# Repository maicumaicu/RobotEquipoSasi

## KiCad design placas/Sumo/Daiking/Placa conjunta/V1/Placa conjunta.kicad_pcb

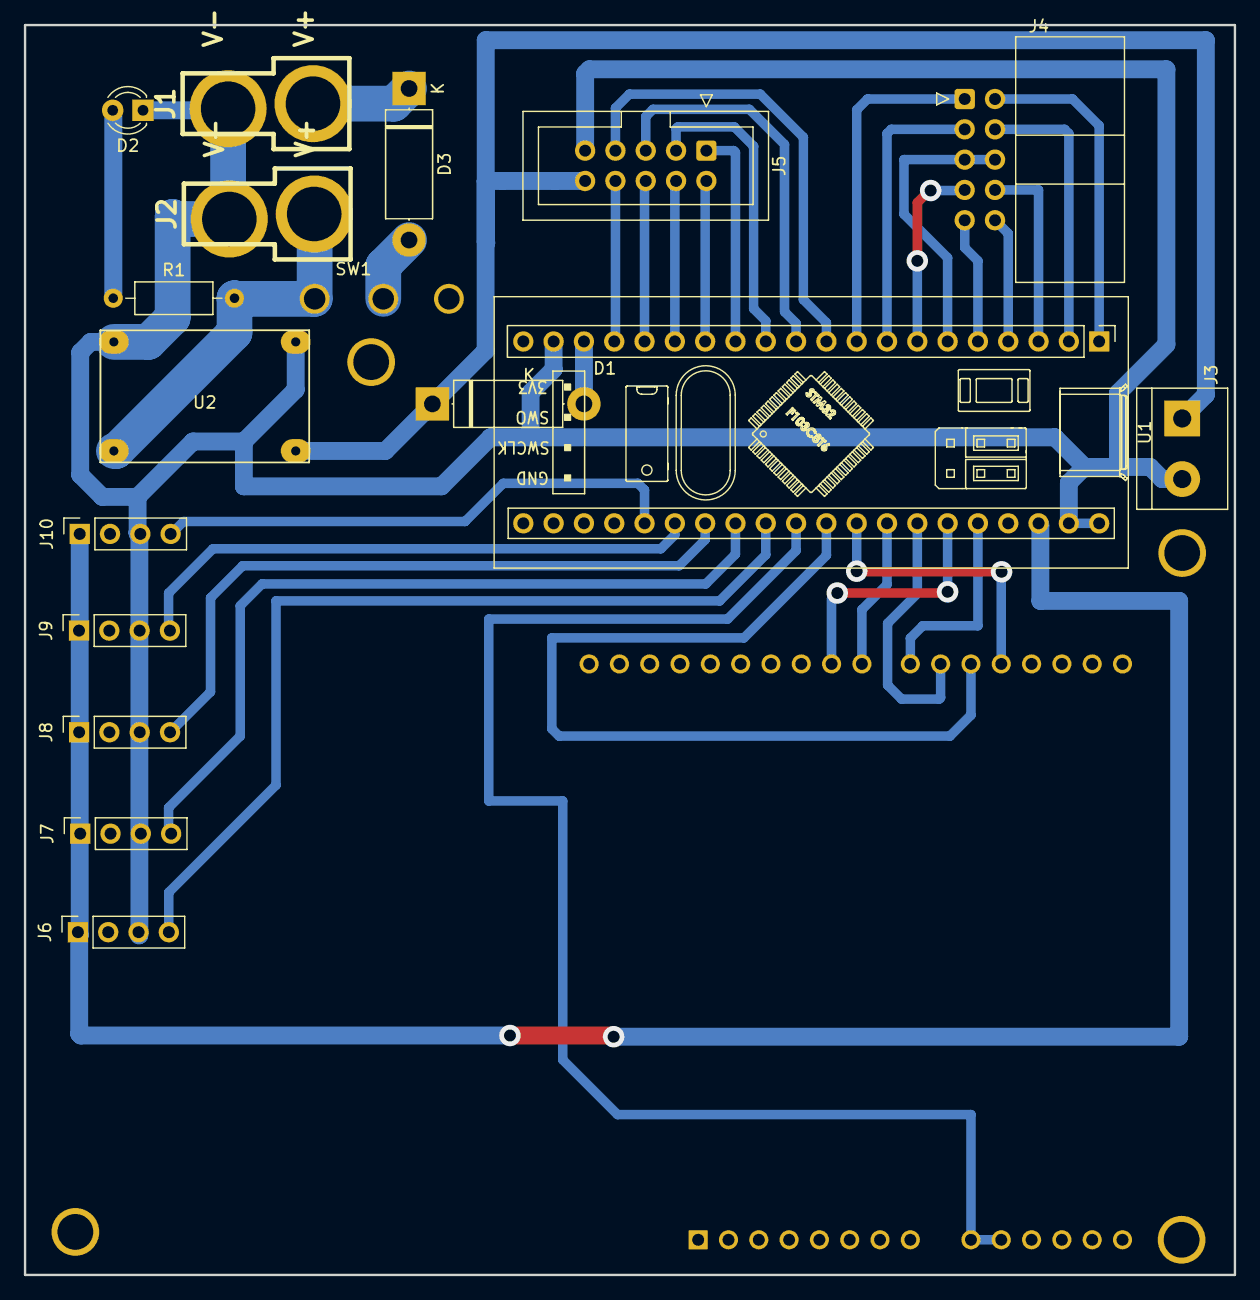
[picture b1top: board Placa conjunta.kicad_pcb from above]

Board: 2 copper layers, 101.4 x 104.7 mm, 18 parts (1 on the bottom side), 37 nets.

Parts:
A1: Arduino_UNO_R3
D1, D3: type="D" model="DIODE" lib=""; D_5W_P12.70mm_Horizontal
D2: LED; LED_D3.0mm
J1: BATERIA1; DEANS
J2: MOTORES; DEANS
J3: Conn_01x02_Male; TerminalBlock_bornier-2_P5.08mm
J4: Control Sensores; IDC-Header_2x05_P2.54mm_Horizontal
J5: Control Botones; IDC-Header_2x05_P2.54mm_Vertical
J6, J7, J8, J9, J10: Conn_01x04_Male; PinSocket_1x04_P2.54mm_Vertical
R1: R; R_Axial_DIN0207_L6.3mm_D2.5mm_P10.16mm_Horizontal
SW1: SW_DPDT_x2; Banana_Jack_3Pin
U1: YAAJ_BluePill_Part_Like_SWD_Breakout; YAAJ_BluePill_1
U2: Mini360; Mini360_step-down

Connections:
/3,3v: J6.1, J7.1, J8.1, J9.1, J10.1, U1.20 (3V3), U1.38 (3V3)
/5v: D1.1 (A), J3.1, J5.10, U2.4 (OUT+)
/38khz: J4.5, J4.6, U1.6 (PA9)
/B1: J5.1, U1.13 (PB5)
/B2: J5.3, U1.12 (PB4)
/B3: J5.5, U1.11 (PB3)
/B4: J5.7, U1.10 (PA15)
/EN1: A1.9 (A0), A1.10 (A1), U1.30 (PA5)
/INA1: A1.22 (D7), U1.36 (PB11)
/INA2: A1.23 (D8), U1.33 (PB0)
/INB1: A1.19 (D4), U1.32 (PA7)
/INB2: A1.24 (D9), U1.35 (PB10)
/L1: J5.2, U1.14 (PB6)
/L2: J5.4, U1.15 (PB7)
/L3: J5.6, U1.16 (PB8)
/L4: J5.8, U1.17 (PB9)
/P1: J6.4, U1.29 (PA4)
/P2: J7.4, U1.28 (PA3)
/P3: J8.4, U1.27 (PA2)
/P4: J9.4, U1.26 (PA1)
/P5: J10.4, U1.25 (PA0)
/PWM1: A1.20 (D5), U1.31 (PA6)
/PWM2: A1.21 (D6), U1.34 (PB1)
/S1: J4.9, U1.5 (PA8)
/S2: J4.7, U1.7 (PA10)
/S3: J4.3, U1.8 (PA11)
/S4: J4.1, U1.9 (PA12)
/S5: J4.10, U1.4 (PB15)
/S6: J4.8, U1.3 (PB14)
/S7: J4.4, U1.2 (PB13)
/S8: J4.2, U1.1 (PB12)
/VCC: D3.1 (A), J1.1
/VIN: J2.1, R1.2, SW1.1 (A), U2.2 (IN+)
GND: D2.1 (K), J1.2, J2.2, J3.2, J5.9, J6.3, J7.3, J8.3, J9.3, J10.3, U1.19 (GND), U1.39 (GND), U1.40 (GND), U2.1 (IN-), U2.3 (OUT-)
unnamed: D1.2 (K), U1.18 (5V)
unnamed: D2.2 (A), R1.1
unnamed: D3.2 (K), SW1.2 (B)

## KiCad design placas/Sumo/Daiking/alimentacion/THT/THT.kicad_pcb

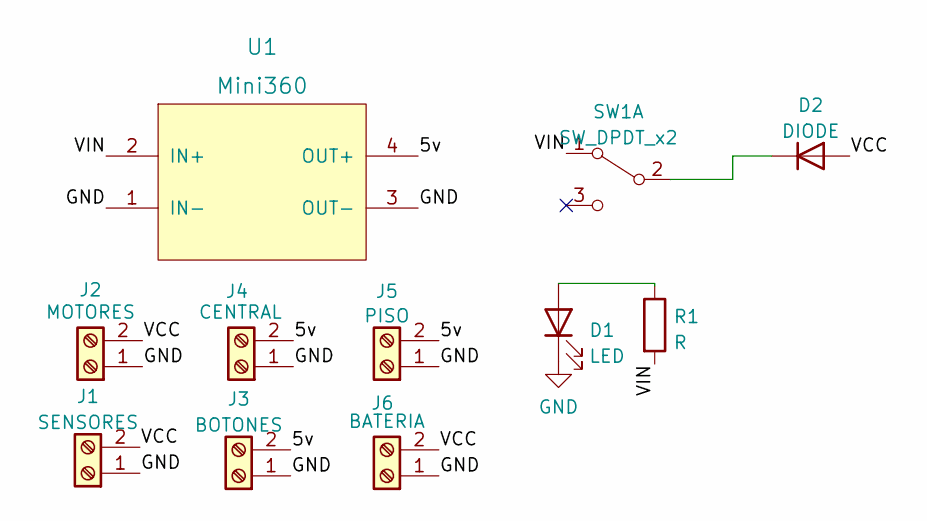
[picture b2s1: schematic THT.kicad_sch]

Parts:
D1: LED; LED_D3.0mm
D2: DIODE; D_5W_P12.70mm_Horizontal
J1: SENSORES; TerminalBlock_bornier-2_P5.08mm
J2: MOTORES; AMASS_XT30U-F_1x02_P5.0mm_Vertical
J3: BOTONES; TerminalBlock_bornier-2_P5.08mm
J4: CENTRAL; TerminalBlock_bornier-2_P5.08mm
J5: PISO; TerminalBlock_bornier-2_P5.08mm
J6: BATERIA; AMASS_XT30U-F_1x02_P5.0mm_Vertical
R1: R; R_Axial_DIN0207_L6.3mm_D2.5mm_P10.16mm_Horizontal
SW1: SW_DPDT_x2; SW_Slide_1P2T_CK_OS102011MS2Q
U1: Mini360; Mini360_step-down

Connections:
/5v: J3.2, J4.2, J5.2, U1.4 (OUT+)
/VCC: D2.1 (A), J1.2, J2.2, J6.2
/VIN: R1.2, SW1.1 (A), U1.2 (IN+)
GND: D1.1 (K), J1.1, J2.1, J3.1, J4.1, J5.1, J6.1, U1.1 (IN-), U1.3 (OUT-)
unnamed: D1.2 (A), R1.1
unnamed: D2.2 (K), SW1.2 (B)

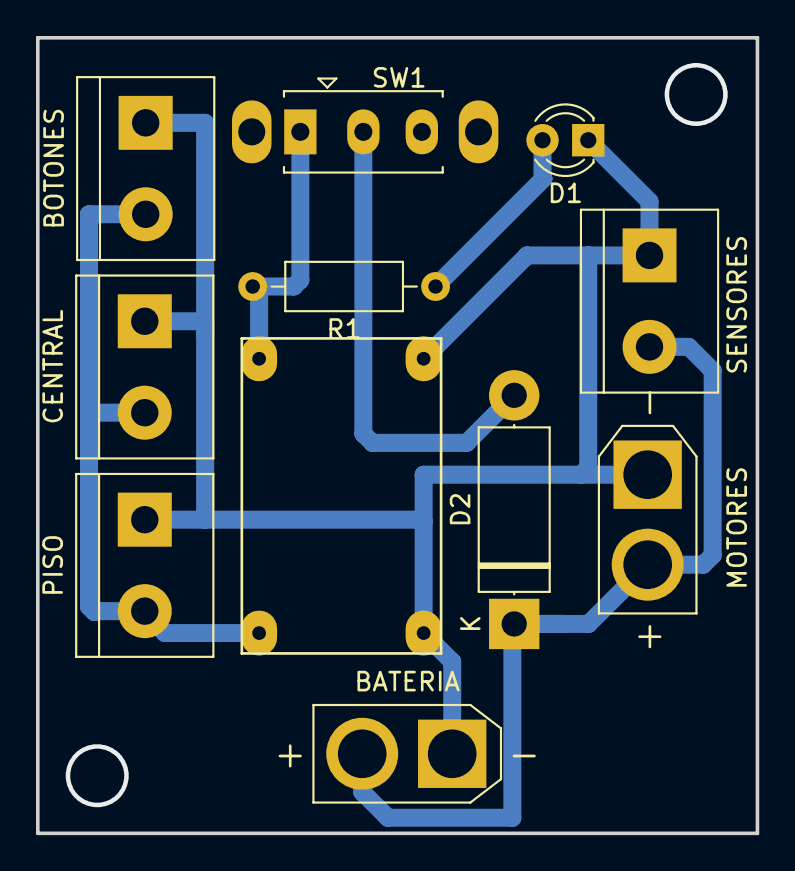
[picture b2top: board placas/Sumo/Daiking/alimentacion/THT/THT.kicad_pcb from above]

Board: 2 copper layers, 40.0 x 44.2 mm, 11 parts (0 on the bottom side), 6 nets.

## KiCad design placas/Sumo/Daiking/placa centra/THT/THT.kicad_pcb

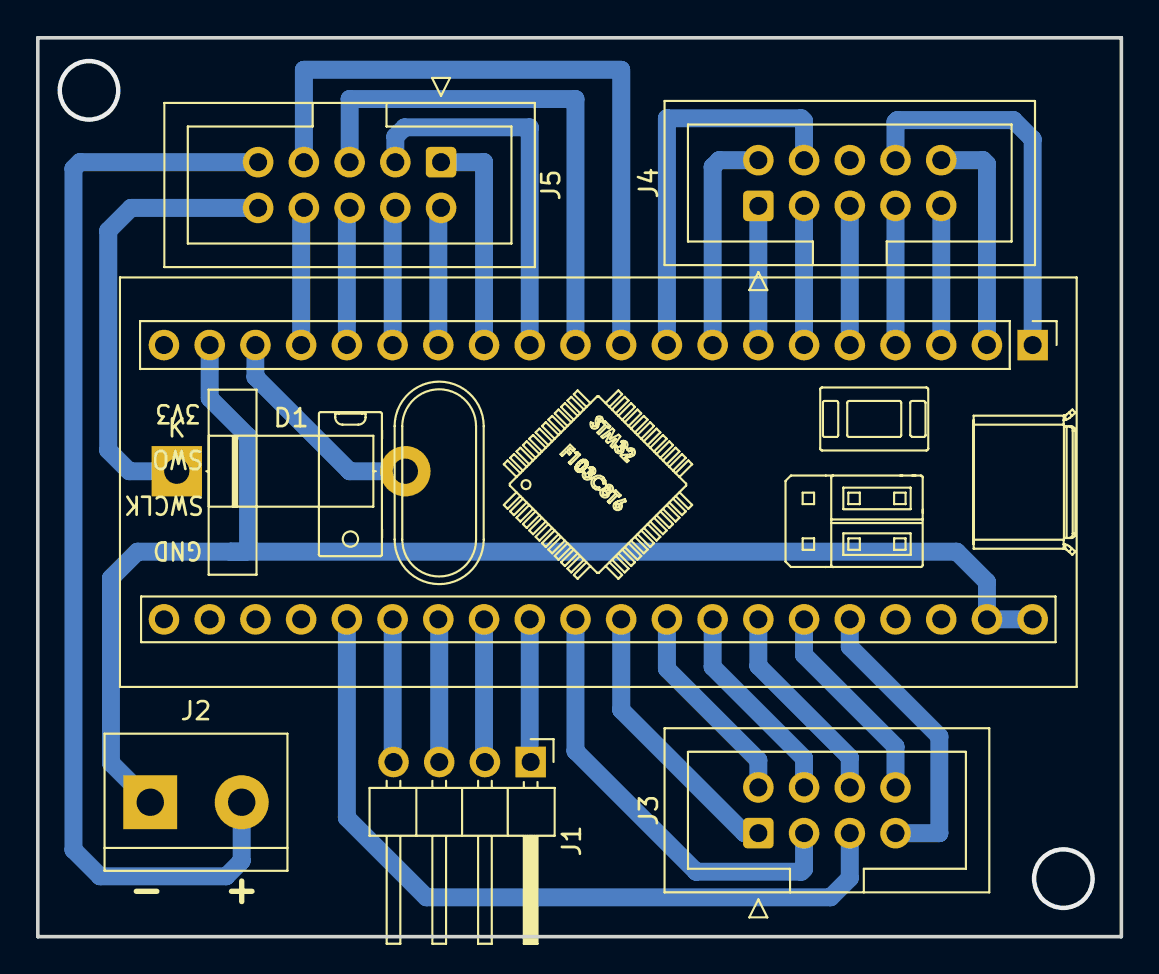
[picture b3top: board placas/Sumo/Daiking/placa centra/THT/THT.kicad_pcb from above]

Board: 2 copper layers, 60.2 x 49.9 mm, 7 parts (0 on the bottom side), 33 nets.

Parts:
D1: DIODE; D_5W_P12.70mm_Horizontal
J1: Control Piso; PinHeader_1x04_P2.54mm_Horizontal
J2: BATERIA; TerminalBlock_bornier-2_P5.08mm
J3: Control Motores; IDC-Header_2x04_P2.54mm_Vertical
J4: Control Sensores; IDC-Header_2x05_P2.54mm_Vertical
J5: Control Botones; IDC-Header_2x05_P2.54mm_Vertical
U1: YAAJ_BluePill_Part_Like_SWD_Breakout; YAAJ_BluePill_SWD_1

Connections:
/5v: D1.2 (K), U1.18 (5V)
/38Kh: J4.5, U1.5 (PA8)
/B1: J5.1, U1.13 (PB5)
/B2: J5.3, U1.12 (PB4)
/B3: J5.5, U1.11 (PB3)
/B4: J5.7, U1.10 (PA15)
/E1: J2.2, J5.9
/E2: D1.1 (A), J5.10
/EN1: J3.3, U1.30 (PA5)
/EN2: J3.4, U1.33 (PB0)
/GND: J2.1, U1.19 (GND), U1.39 (GND), U1.40 (GND)
/INA1: J3.7, U1.36 (PB11)
/INA2: J3.2, U1.32 (PA7)
/INB1: J3.1, U1.31 (PA6)
/INB2: J3.8, U1.35 (PB10)
/L1: J5.2, U1.14 (PB6)
/L2: J5.4, U1.15 (PB7)
/L3: J5.6, U1.16 (PB8)
/L4: J5.8, U1.17 (PB9)
/P1: J1.1, U1.29 (PA4)
/P2: J1.2, U1.28 (PA3)
/P3: J1.3, U1.27 (PA2)
/P4: J1.4, U1.26 (PA1)
/PWM1: J3.5, U1.25 (PA0)
/PWM2: J3.6, U1.34 (PB1)
/S1: J4.3, U1.6 (PA9)
/S2: J4.1, U1.7 (PA10)
/S3: J4.2, U1.8 (PA11)
/S4: J4.4, U1.9 (PA12)
/S5: J4.7, U1.4 (PB15)
/S6: J4.9, U1.3 (PB14)
/S7: J4.10, U1.2 (PB13)
/S8: J4.8, U1.1 (PB12)

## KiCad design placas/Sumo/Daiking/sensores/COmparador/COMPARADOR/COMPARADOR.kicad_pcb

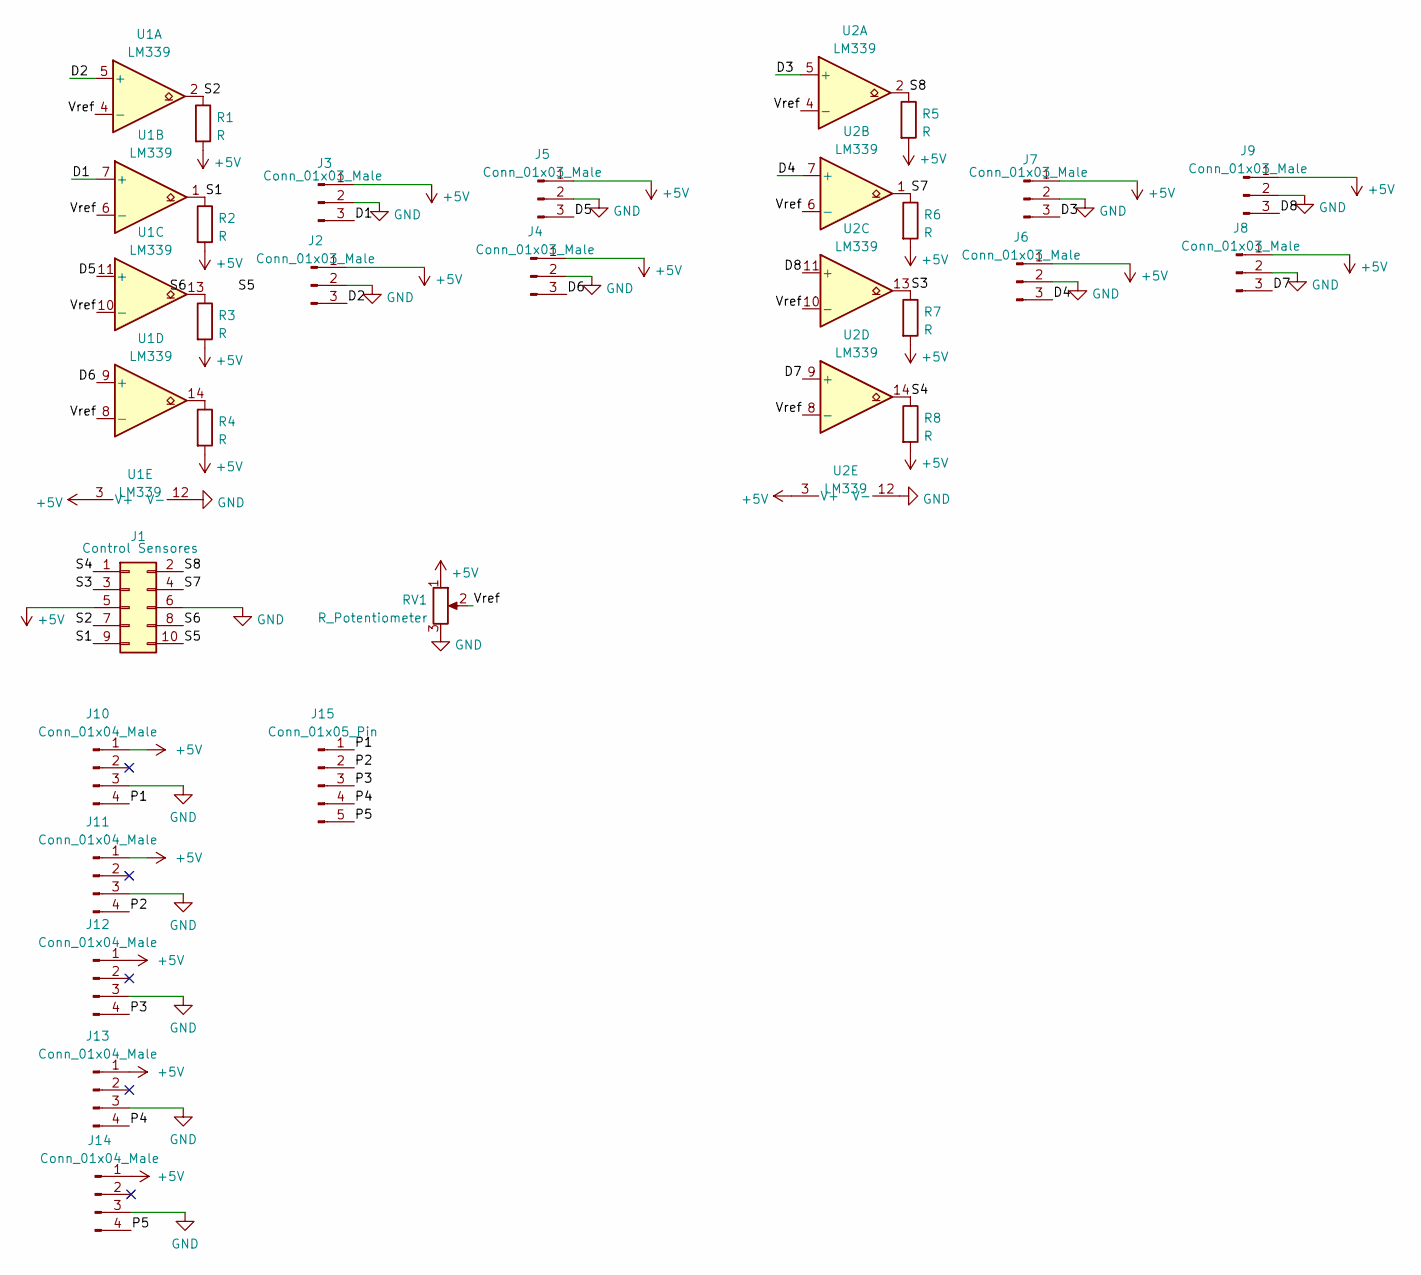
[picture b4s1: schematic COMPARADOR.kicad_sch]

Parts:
J1: Control Sensores; IDC-Header_2x05_P2.54mm_Horizontal
J2, J3, J4, J5, J6, J7, J8, J9: Conn_01x03_Male; PinHeader_1x03_P2.54mm_Vertical
J10, J11, J12, J13, J14: Conn_01x04_Male; PinSocket_1x04_P2.54mm_Vertical
J15: Conn_01x05_Pin; PinHeader_1x05_P2.54mm_Horizontal
R1, R2, R3, R4, R5, R6, R7, R8: R; R_Axial_DIN0207_L6.3mm_D2.5mm_P10.16mm_Horizontal
RV1: R_Potentiometer; Potentiometer_Bourns_3299W_Vertical
U1, U2: LM339; DIP-14_W7.62mm_Socket_LongPads

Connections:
+5V: J1.5, J2.1, J3.1, J4.1, J5.1, J6.1, J7.1, J8.1, J9.1, J10.1, J11.1, J12.1, J13.1, J14.1, R1.2, R2.2, R3.2, R4.2, R5.2, R6.2, R7.2, R8.2, RV1.1, U1.3 (V+), U2.3 (V+)
/D1: J3.3, U1.7 (+)
/D2: J2.3, U1.5 (+)
/D3: J7.3, U2.5 (+)
/D4: J6.3, U2.7 (+)
/D5: J5.3, U1.11 (+)
/D6: J4.3, U1.9 (+)
/D7: J8.3, U2.9 (+)
/D8: J9.3, U2.11 (+)
/P1: J10.4, J15.1
/P2: J11.4, J15.2
/P3: J12.4, J15.3
/P4: J13.4, J15.4
/P5: J14.4, J15.5
/S1: J1.9, R2.1, U1.1
/S2: J1.7, R1.1, U1.2
/S3: J1.3, R7.1, U2.13
/S4: J1.1, R8.1, U2.14
/S5: J1.10
/S6: J1.8
/S7: J1.4, R6.1, U2.1
/S8: J1.2, R5.1, U2.2
/Vref: RV1.2, U1.4 (-), U1.6 (-), U1.8 (-), U1.10 (-), U2.4 (-), U2.6 (-), U2.8 (-), U2.10 (-)
GND: J1.6, J2.2, J3.2, J4.2, J5.2, J6.2, J7.2, J8.2, J9.2, J10.3, J11.3, J12.3, J13.3, J14.3, RV1.3, U1.12 (V-), U2.12 (V-)
unnamed: R3.1, U1.13
unnamed: R4.1, U1.14

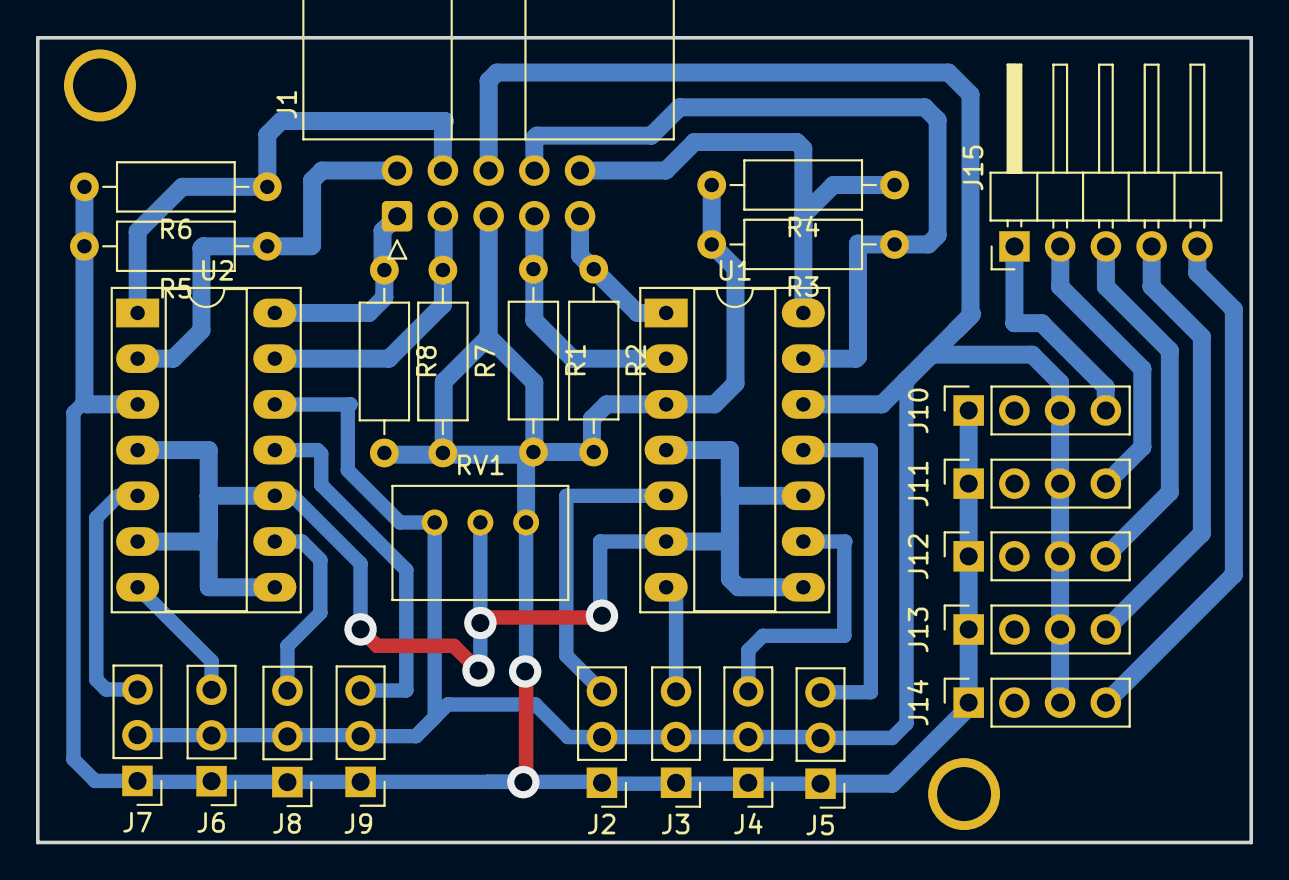
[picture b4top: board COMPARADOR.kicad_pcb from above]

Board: 2 copper layers, 67.4 x 44.7 mm, 26 parts (0 on the bottom side), 24 nets.

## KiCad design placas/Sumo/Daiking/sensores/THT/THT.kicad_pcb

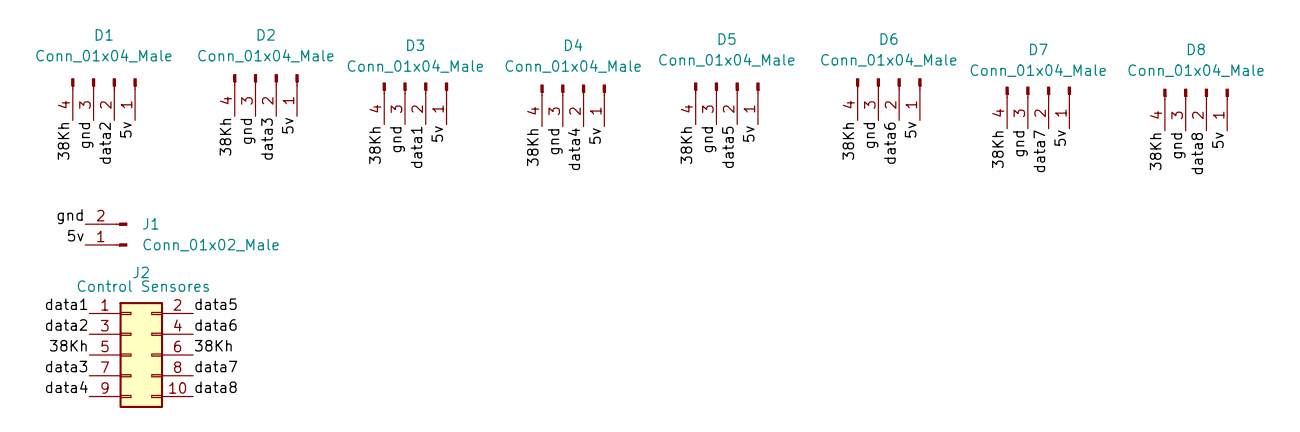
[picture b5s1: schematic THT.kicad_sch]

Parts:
D1, D2, D3, D4: Conn_01x04_Male
D5, D6, D7, D8: Conn_01x04_Male; PinHeader_1x04_P2.54mm_Vertical
J1: Conn_01x02_Male; TerminalBlock_bornier-2_P5.08mm
J2: Control Sensores; IDC-Header_2x05_P2.54mm_Vertical

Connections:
/5v: D1.1, D2.1, D3.1, D4.1, D5.1, D6.1, D7.1, D8.1, J1.1
/38Kh: D1.4, D2.4, D3.4, D4.4, D5.4, D6.4, D7.4, D8.4, J2.5, J2.6
/data1: D3.2, J2.1
/data2: D1.2, J2.3
/data3: D2.2, J2.7
/data4: D4.2, J2.9
/data5: D5.2, J2.2
/data6: D6.2, J2.4
/data7: D7.2, J2.8
/data8: D8.2, J2.10
/gnd: D1.3, D2.3, D3.3, D4.3, D5.3, D6.3, D7.3, D8.3, J1.2

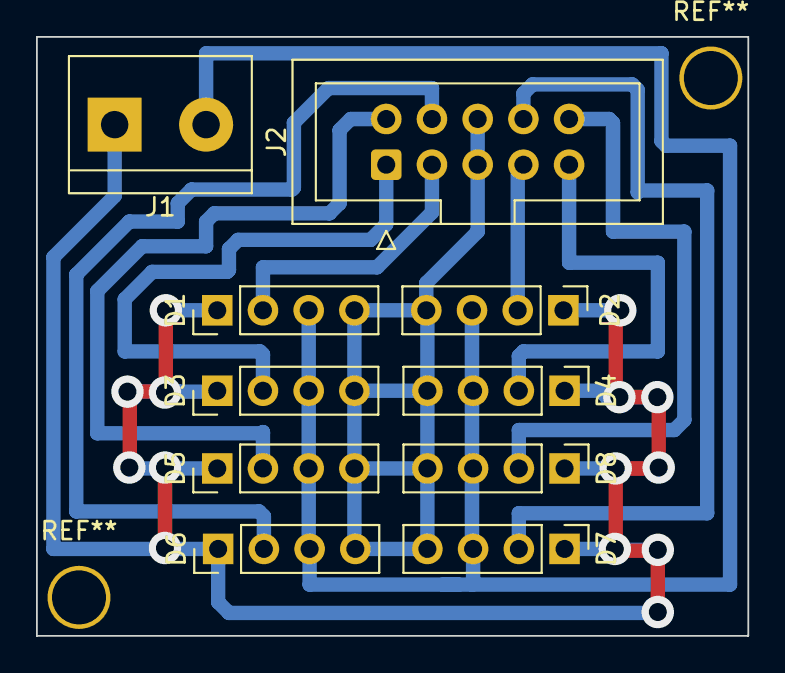
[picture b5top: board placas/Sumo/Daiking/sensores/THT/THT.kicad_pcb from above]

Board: 2 copper layers, 39.5 x 33.3 mm, 10 parts (0 on the bottom side), 11 nets.

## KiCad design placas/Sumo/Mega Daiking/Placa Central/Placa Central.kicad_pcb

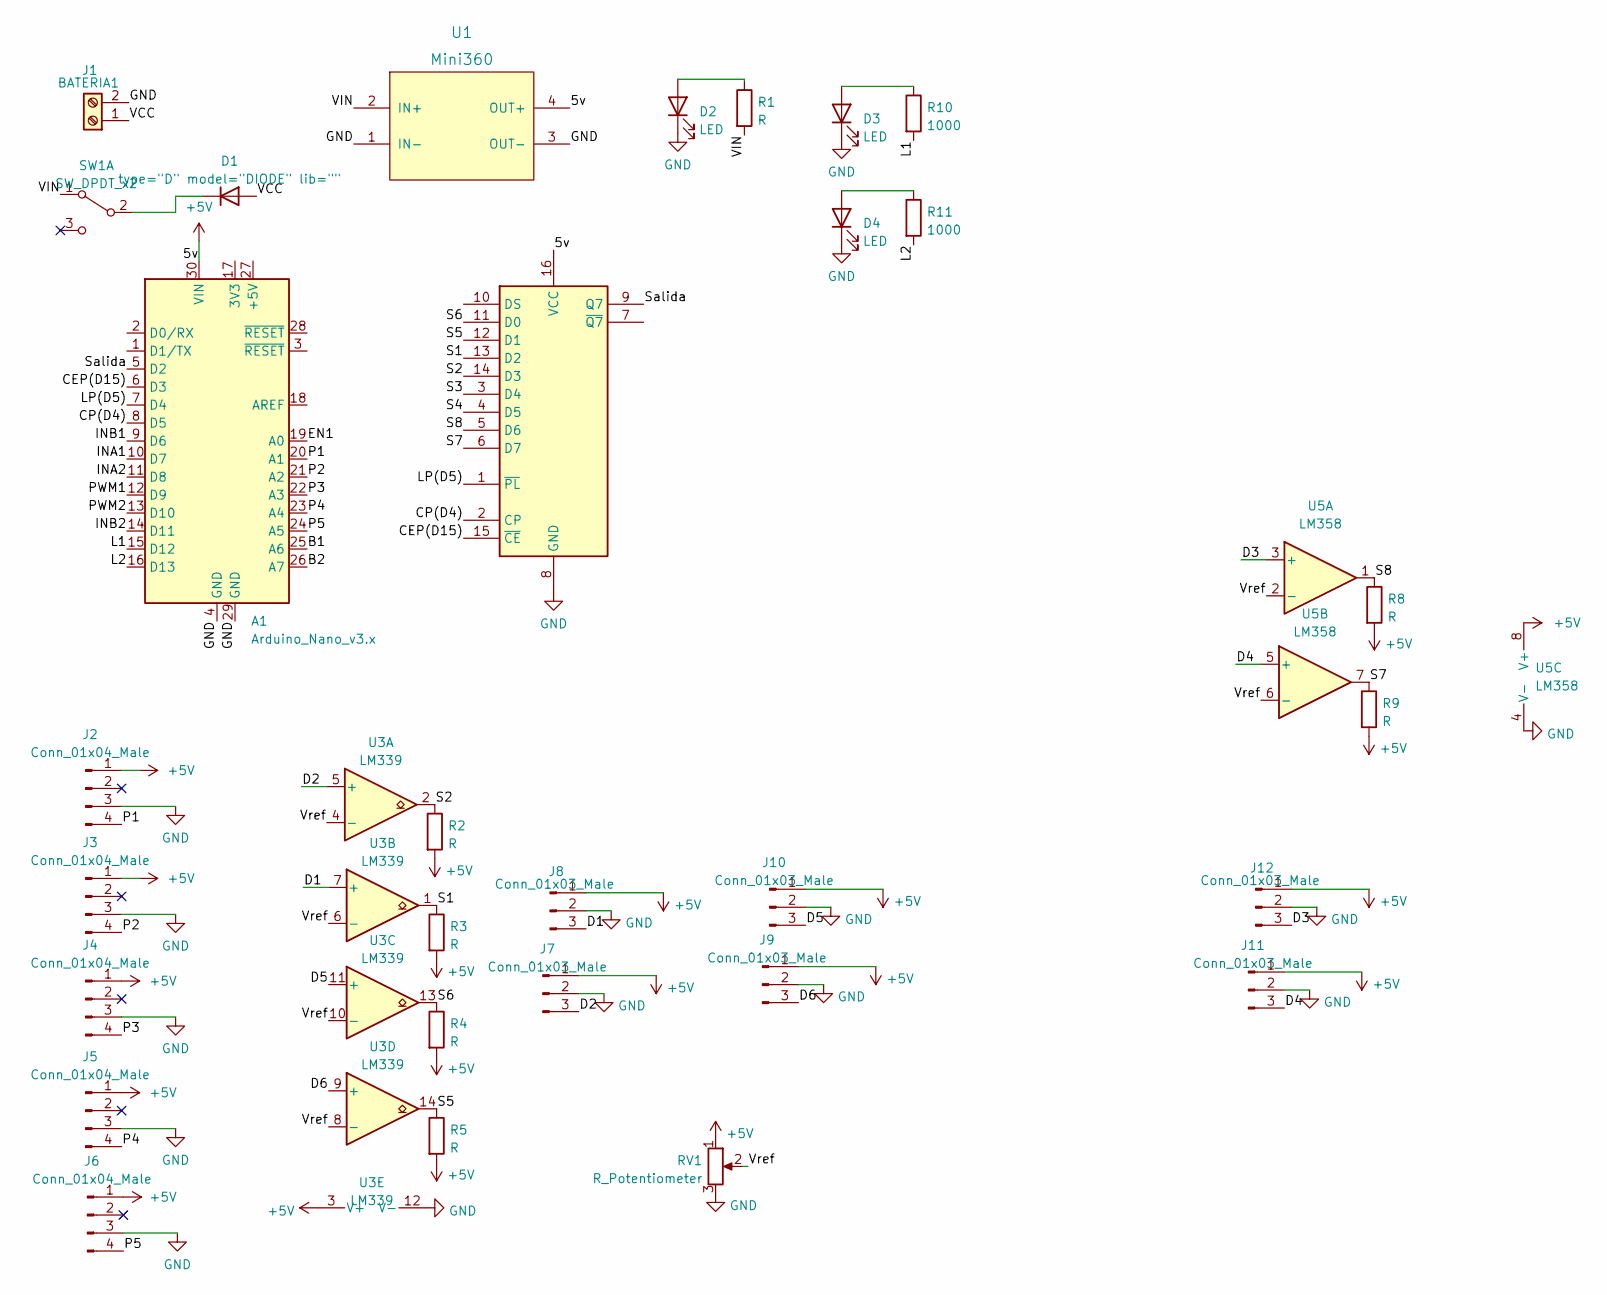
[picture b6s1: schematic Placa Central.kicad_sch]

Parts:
A1: Arduino_Nano_v3.x; Arduino_Nano
D1: type="D" model="DIODE" lib=""; D_5W_P12.70mm_Horizontal
D2, D3, D4: LED; LED_D3.0mm
J1: BATERIA1; DEANS
J2, J3, J4, J5, J6: Conn_01x04_Male; PinSocket_1x04_P2.54mm_Vertical
J7, J8, J9, J10, J11, J12: Conn_01x03_Male; PinHeader_1x03_P2.54mm_Vertical
R1, R2, R3, R4, R5, R8, R9: R; R_1206_3216Metric_Pad1.30x1.75mm_HandSolder
R10, R11: 1000; R_1206_3216Metric_Pad1.30x1.75mm_HandSolder
RV1: R_Potentiometer; Potentiometer_Bourns_3299W_Vertical
SW1: SW_DPDT_x2; SW_CuK_JS202011CQN_DPDT_Straight
U1: Mini360; Mini360_step-down
U2: 74LS165; DIP-16_W7.62mm_Socket_LongPads
U3: LM339; SO-14_3.9x8.65mm_P1.27mm
U5: LM358; SO-8_3.9x4.9mm_P1.27mm

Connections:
+5V: A1.30 (VIN), J2.1, J3.1, J4.1, J5.1, J6.1, J7.1, J8.1, J9.1, J10.1, J11.1, J12.1, R2.2, R3.2, R4.2, R5.2, R8.2, R9.2, RV1.1, U1.4 (OUT+), U2.16 (VCC), U3.3 (V+), U5.8 (V+)
/B1: A1.25 (A6)
/B2: A1.26 (A7)
/CEP(D15): A1.6 (D3), U2.15 (~CE)
/CP(D4): A1.8 (D5), U2.2 (CP)
/D1: J8.3, U3.7 (+)
/D2: J7.3, U3.5 (+)
/D3: J12.3, U5.3 (+)
/D4: J11.3, U5.5 (+)
/D5: J10.3, U3.11 (+)
/D6: J9.3, U3.9 (+)
/EN1: A1.19 (A0)
/INA1: A1.10 (D7)
/INA2: A1.11 (D8)
/INB1: A1.9 (D6)
/INB2: A1.14 (D11)
/L1: A1.15 (D12), R10.2
/L2: A1.16 (D13), R11.2
/LP(D5): A1.7 (D4), U2.1 (~PL)
/P1: A1.20 (A1), J2.4
/P2: A1.21 (A2), J3.4
/P3: A1.22 (A3), J4.4
/P4: A1.23 (A4), J5.4
/P5: A1.24 (A5), J6.4
/PWM1: A1.12 (D9)
/PWM2: A1.13 (D10)
/S1: R3.1, U2.13 (D2), U3.1
/S2: R2.1, U2.14 (D3), U3.2
/S3: U2.3 (D4)
/S4: U2.4 (D5)
/S5: R5.1, U2.12 (D1), U3.14
/S6: R4.1, U2.11 (D0), U3.13
/S7: R9.1, U2.6 (D7), U5.7
/S8: R8.1, U2.5 (D6), U5.1
/Salida: A1.5 (D2), U2.9 (Q7)
/VCC: D1.1 (A), J1.1
/VIN: R1.2, SW1.1 (A), U1.2 (IN+)
/Vref: RV1.2, U3.4 (-), U3.6 (-), U3.8 (-), U3.10 (-), U5.2 (-), U5.6 (-)
GND: A1.4 (GND), A1.29 (GND), D2.1 (K), D3.1 (K), D4.1 (K), J1.2, J2.3, J3.3, J4.3, J5.3, J6.3, J7.2, J8.2, J9.2, J10.2, J11.2, J12.2, RV1.3, U1.1 (IN-), U1.3 (OUT-), U2.8 (GND), U3.12 (V-), U5.4 (V-)
unnamed: D1.2 (K), SW1.2 (B)
unnamed: D2.2 (A), R1.1
unnamed: D3.2 (A), R10.1
unnamed: D4.2 (A), R11.1

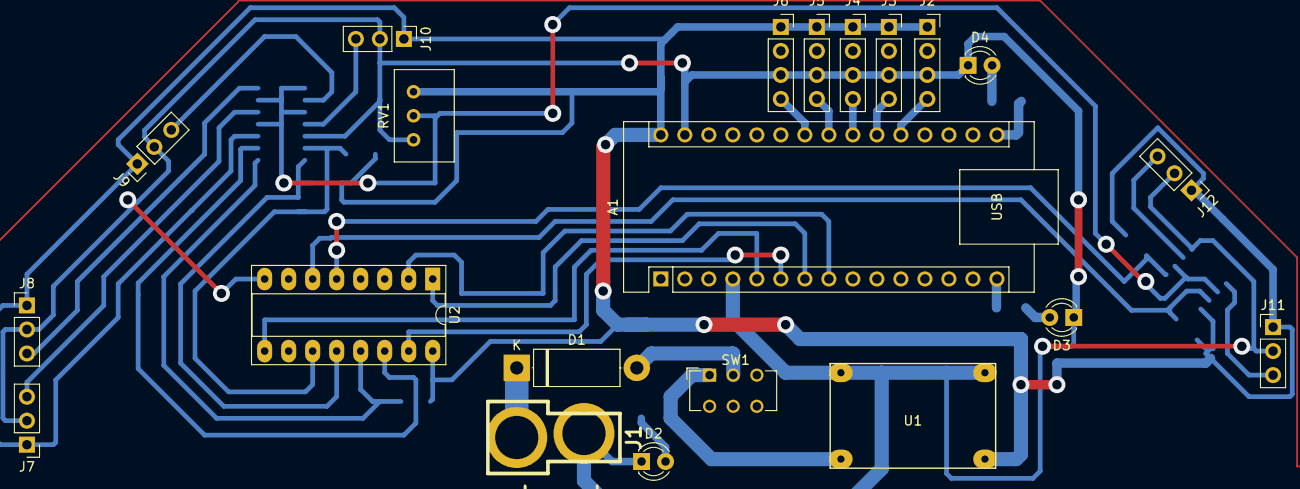
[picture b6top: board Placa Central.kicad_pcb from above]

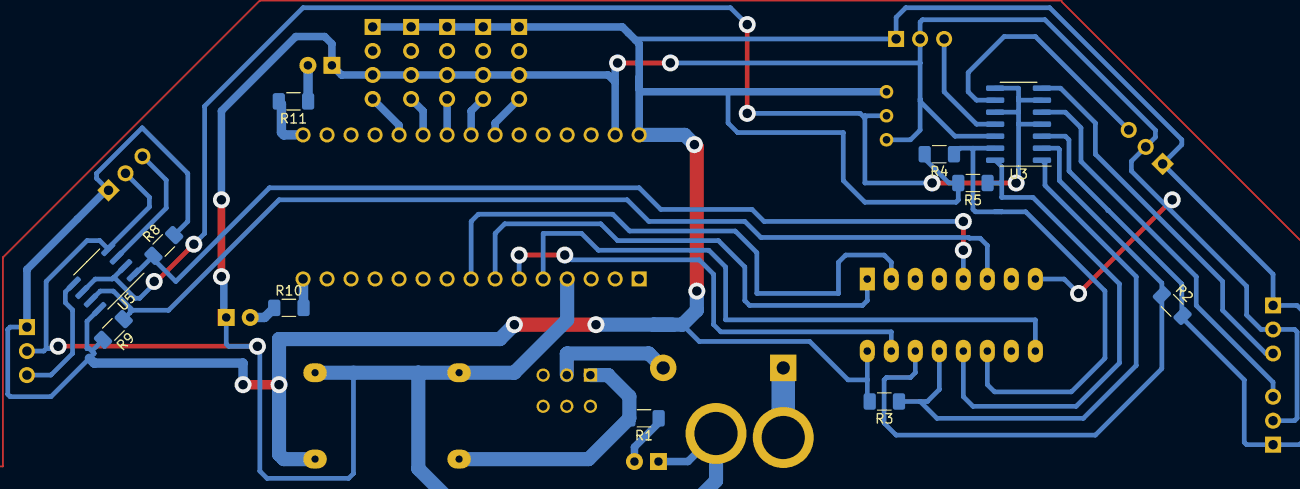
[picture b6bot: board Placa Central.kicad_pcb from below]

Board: 2 copper layers, 32 parts (11 on the bottom side), 32 nets.

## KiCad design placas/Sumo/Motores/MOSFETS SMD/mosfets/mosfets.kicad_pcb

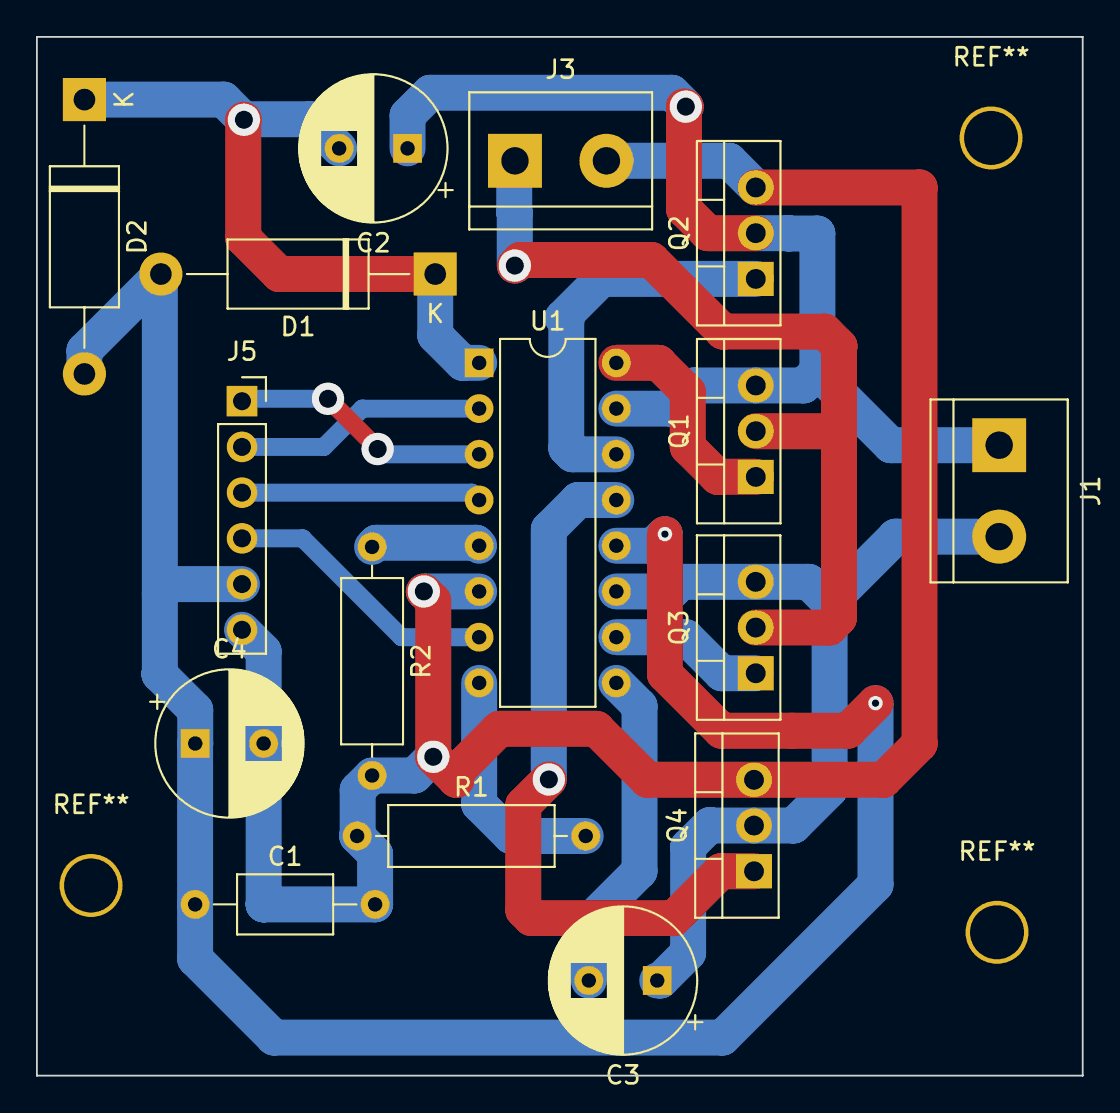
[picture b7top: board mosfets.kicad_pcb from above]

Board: 2 copper layers, 58.1 x 57.7 mm, 16 parts (0 on the bottom side), 17 nets.

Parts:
C1: C; C_Axial_L5.1mm_D3.1mm_P10.00mm_Horizontal
C2, C3, C4: 47nf; CP_Radial_D8.0mm_P3.80mm
D1, D2: D; D_DO-15_P15.24mm_Horizontal
J1, J3: Screw_Terminal_01x02; TerminalBlock_bornier-2_P5.08mm
J5: Conn_01x06_Pin; PinSocket_1x06_P2.54mm_Vertical
Q1, Q2, Q3, Q4: IRLZ44N; TO-220-3_Vertical
R1, R2: 36k; R_Axial_DIN0309_L9.0mm_D3.2mm_P12.70mm_Horizontal
U1: HIP4082xP; DIP-16_W7.62mm

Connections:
+5V: C1.1, C4.1, D1.2 (A), D2.2 (A), J5.5, U1.12 (VDD)
GND: C1.2, C4.2, J3.2, J5.6, Q2.3 (S), Q4.3 (S), R1.1, R2.2, U1.6 (VSS)
unnamed: C2.2, D1.1 (K), D2.1 (K), U1.1 (BHB)
unnamed: C2.1, J1.1, Q1.3 (S), Q2.2 (D), U1.15 (BHS)
unnamed: C3.1, J1.2, Q3.3 (S), Q4.2 (D), U1.11 (AHS)
unnamed: J5.1, U1.3 (BLI)
unnamed: J5.2, U1.2 (BHI)
unnamed: J5.3, U1.4 (ALI)
unnamed: J5.4, U1.7 (AHI)
unnamed: Q1.1 (G), U1.16 (BHO)
unnamed: Q2.1 (G), U1.14 (BLO)
unnamed: Q3.1 (G), U1.10 (AHO)
unnamed: Q4.1 (G), U1.13 (ALO)
unnamed: C3.2, U1.9 (AHB)
unnamed: R2.1, U1.5 (DEL)
unnamed: R1.2, U1.8 (DIS)
VDD: J3.1, Q1.2 (D), Q3.2 (D)
